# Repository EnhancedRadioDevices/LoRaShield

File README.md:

LoRaShield2.1 Hardware

These are the hardware design files for the LoRaShield2.1 electronics.

These hardware files were created with KiCAD. 
You may need the KiCAD libraries available here: https://github.com/mogar/KiCAD_libs
When opening these projects in KiCAD, you may need to change the path to the libraries from the above link.
This can be done in preferences->libraries in both the schematic editor and the layout editor.
Make sure the libraries noted there point to wherever you put the above KiCAD_libs repo.

# Arduino Library

Check out these libraries:

* https://github.com/EnhancedRadioDevices/LoRaHam
* https://github.com/EnhancedRadioDevices/LoRaChat

# LoRaShield 2.1 Pinout

LoRaShield uses the SPI pins on your Arduino. It also uses a couple of digital pins for reset and interrupt.

    Arduino <-> LoRaShield
    D2          interrupt
    D3          reset
    D10         SPI SS
    D11         SPI MOSI
    D12         SPI MISO
    D13         SPI SCK

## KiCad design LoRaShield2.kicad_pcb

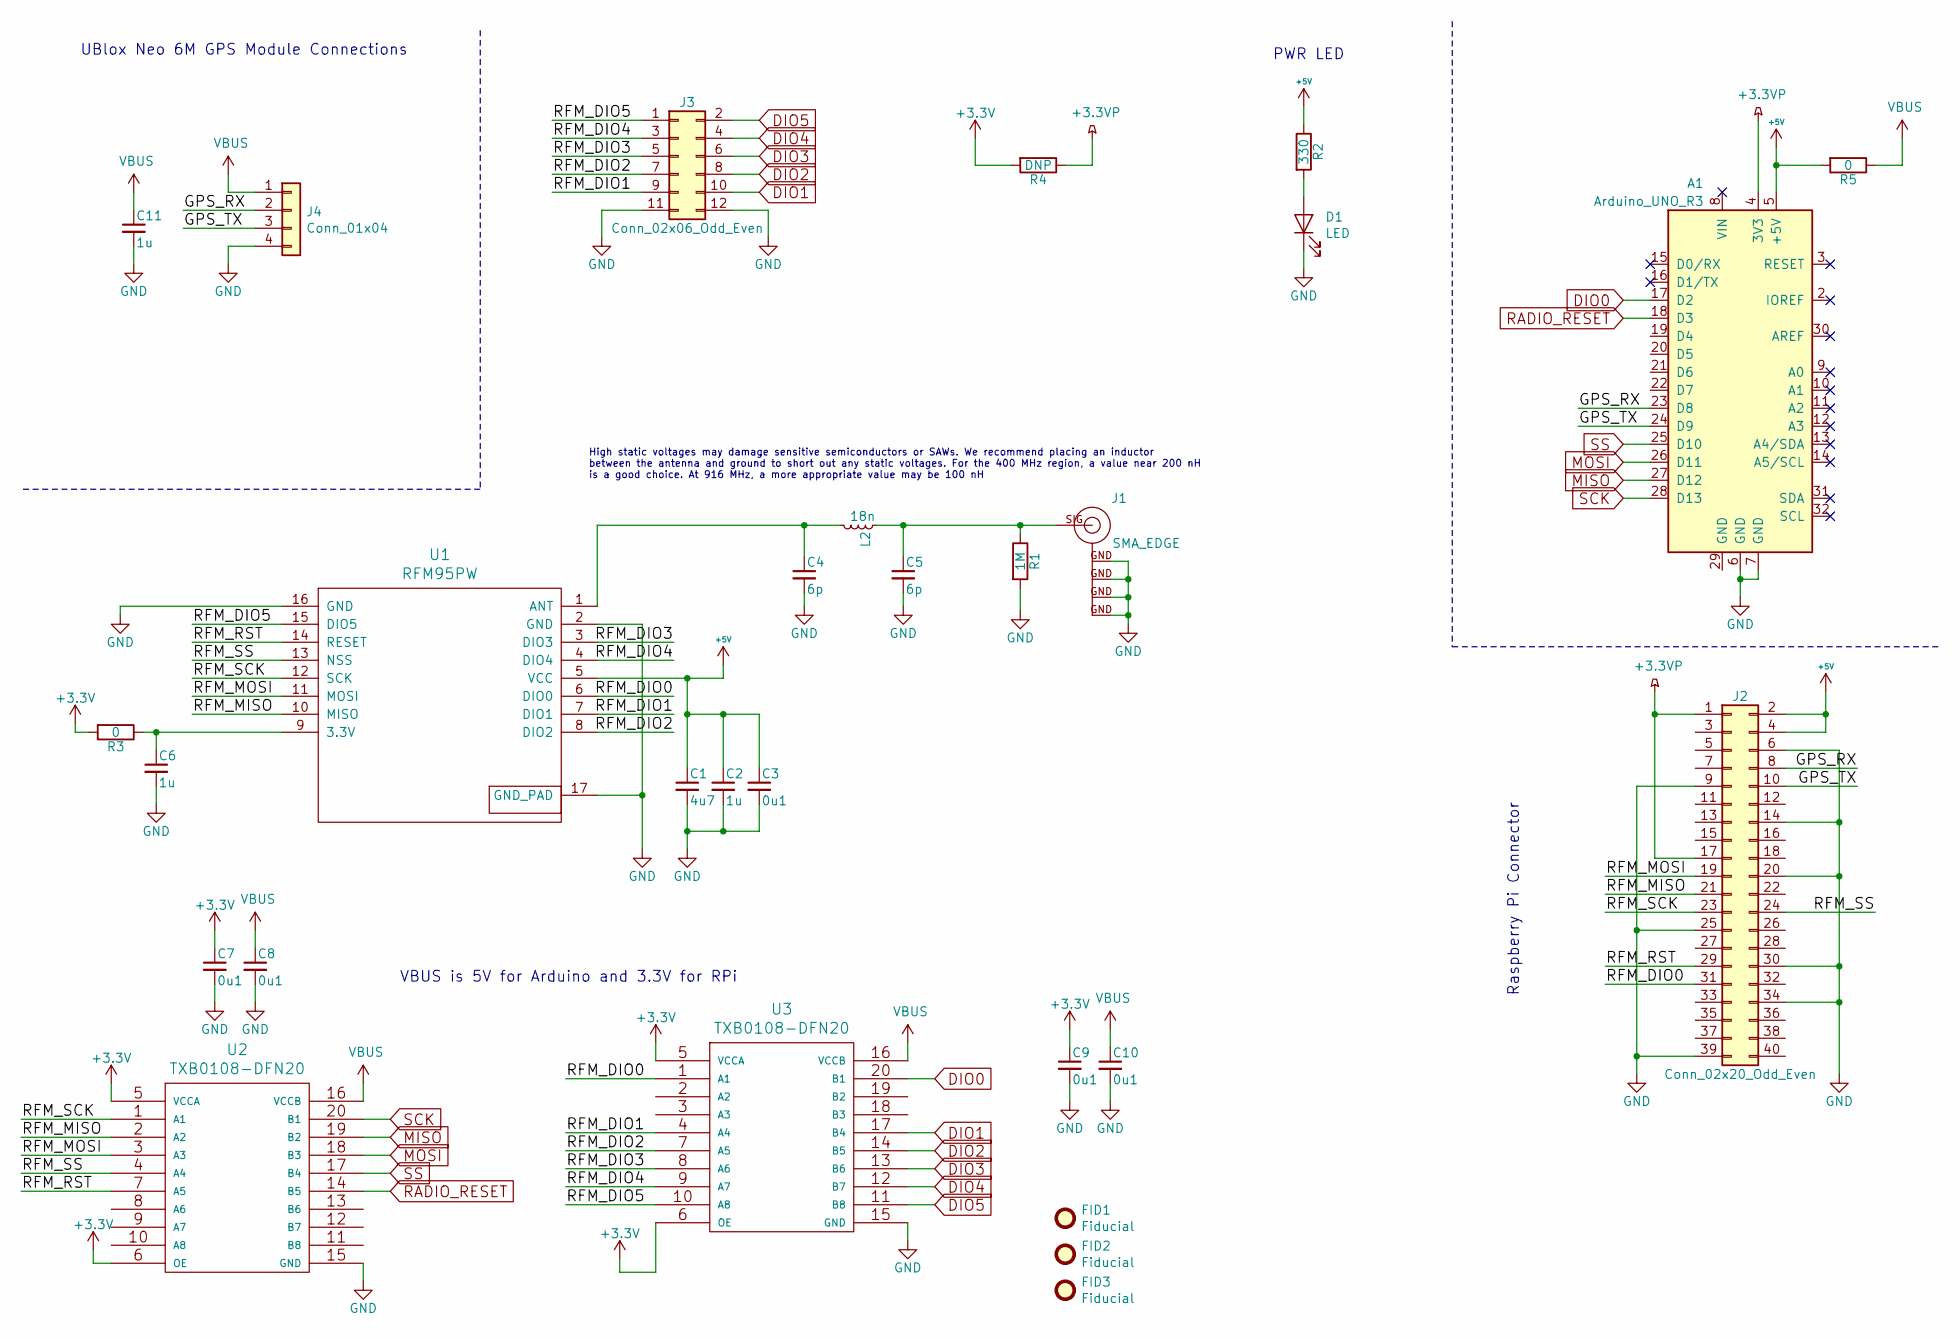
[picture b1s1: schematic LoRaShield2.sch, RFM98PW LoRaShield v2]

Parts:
A1: Arduino_UNO_R3; Arduino_UNO_HamShieldFootprint
C1: 4u7; C_0603
C2, C6, C11: 1u; C_0603
C3, C7, C8, C9, C10: 0u1; C_0603
C4, C5: 6p; C_0603
D1: LED; D_0603
FID1, FID2, FID3: Fiducial; Fiducial_0.5mm_Dia_1mm_Outer
J1: SMA_EDGE; SMA-EDGE-HandSolder
J2: Conn_02x20_Odd_Even; Pin_Header_Straight_2x20_Pitch2.54mm
J3: Conn_02x06_Odd_Even; Pin_Header_Straight_2x06_Pitch2.54mm
J4: Conn_01x04; Pin_Header_Straight_1x04_Pitch2.54mm
L2: 18n; L_0603
R1: 1M; R_0603
R2: 330; R_0603
R3, R5: 0; R_0402
R4: DNP; R_0402
U1: RFM95PW; RFM98PW
U2, U3: TXB0108-DFN20; USON-20_2x4mm_Pitch0.4mm

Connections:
+3.3VP: A1.4 (3V3), J2.1, J2.17, R4.1
+3V3: C7.1, C9.1, R3.2, R4.2, U2.5 (VCCA), U2.6 (OE), U3.5 (VCCA), U3.6 (OE)
+5V: A1.5 (+5V), C1.1, C2.1, C3.1, J2.2, J2.4, R2.1, R5.2, U1.5 (VCC)
/GPS_RX: A1.23 (D8), J2.8, J4.2
/GPS_TX: A1.24 (D9), J2.10, J4.3
/RFM_DIO0: J2.31, U1.6 (DIO0), U3.1 (A1)
/RFM_DIO1: J3.9, U1.7 (DIO1), U3.4 (A4)
/RFM_DIO2: J3.7, U1.8 (DIO2), U3.7 (A5)
/RFM_DIO3: J3.5, U1.3 (DIO3), U3.8 (A6)
/RFM_DIO4: J3.3, U1.4 (DIO4), U3.9 (A7)
/RFM_DIO5: J3.1, U1.15 (DIO5), U3.10 (A8)
/RFM_MISO: J2.21, U1.10 (MISO), U2.2 (A2)
/RFM_MOSI: J2.19, U1.11 (MOSI), U2.3 (A3)
/RFM_RST: J2.29, U1.14 (RESET), U2.7 (A5)
/RFM_SCK: J2.23, U1.12 (SCK), U2.1 (A1)
/RFM_SS: J2.24, U1.13 (NSS), U2.4 (A4)
DIO0: A1.17 (D2), U3.20 (B1)
DIO1: J3.10, U3.17 (B4)
DIO2: J3.8, U3.14 (B5)
DIO3: J3.6, U3.13 (B6)
DIO4: J3.4, U3.12 (B7)
DIO5: J3.2, U3.11 (B8)
GND: A1.6 (GND), A1.7 (GND), C1.2, C2.2, C3.2, C4.2, C5.2, C6.2, C7.2, C8.2, C9.2, C10.2, C11.2, D1.1 (K), J1.GND, J2.6, J2.9, J2.14, J2.20, J2.25, J2.30, J2.34, J2.39, J3.11, J3.12, J4.4, R1.2, U1.2 (GND), U1.16 (GND), U1.17 (GND_PAD), U2.15 (GND), U3.15 (GND)
MISO: A1.27 (D12), U2.19 (B2)
MOSI: A1.26 (D11), U2.18 (B3)
unnamed: C4.1, L2.2, U1.1 (ANT)
unnamed: C5.1, J1.SIG (SIGNAL), L2.1, R1.1
unnamed: C6.1, R3.1, U1.9 (3.3V)
unnamed: D1.2 (A), R2.2
RADIO_RESET: A1.18 (D3), U2.14 (B5)
SCK: A1.28 (D13), U2.20 (B1)
SS: A1.25 (D10), U2.17 (B4)
VBUS: C8.1, C10.1, C11.1, J4.1, R5.1, U2.16 (VCCB), U3.16 (VCCB)

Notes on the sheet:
High static voltages may damage sensitive semiconductors or SAWs. We recommend placing an inductor between the antenna and ground to short out any static voltages. For the 400 MHz region, a value near 200 nH is a good choice. At 916 MHz, a more appropriate value may be 100 nH
Raspberry Pi Connector
VBUS is 5V for Arduino and 3.3V for RPi
PWR LED
UBlox Neo 6M GPS Module Connections

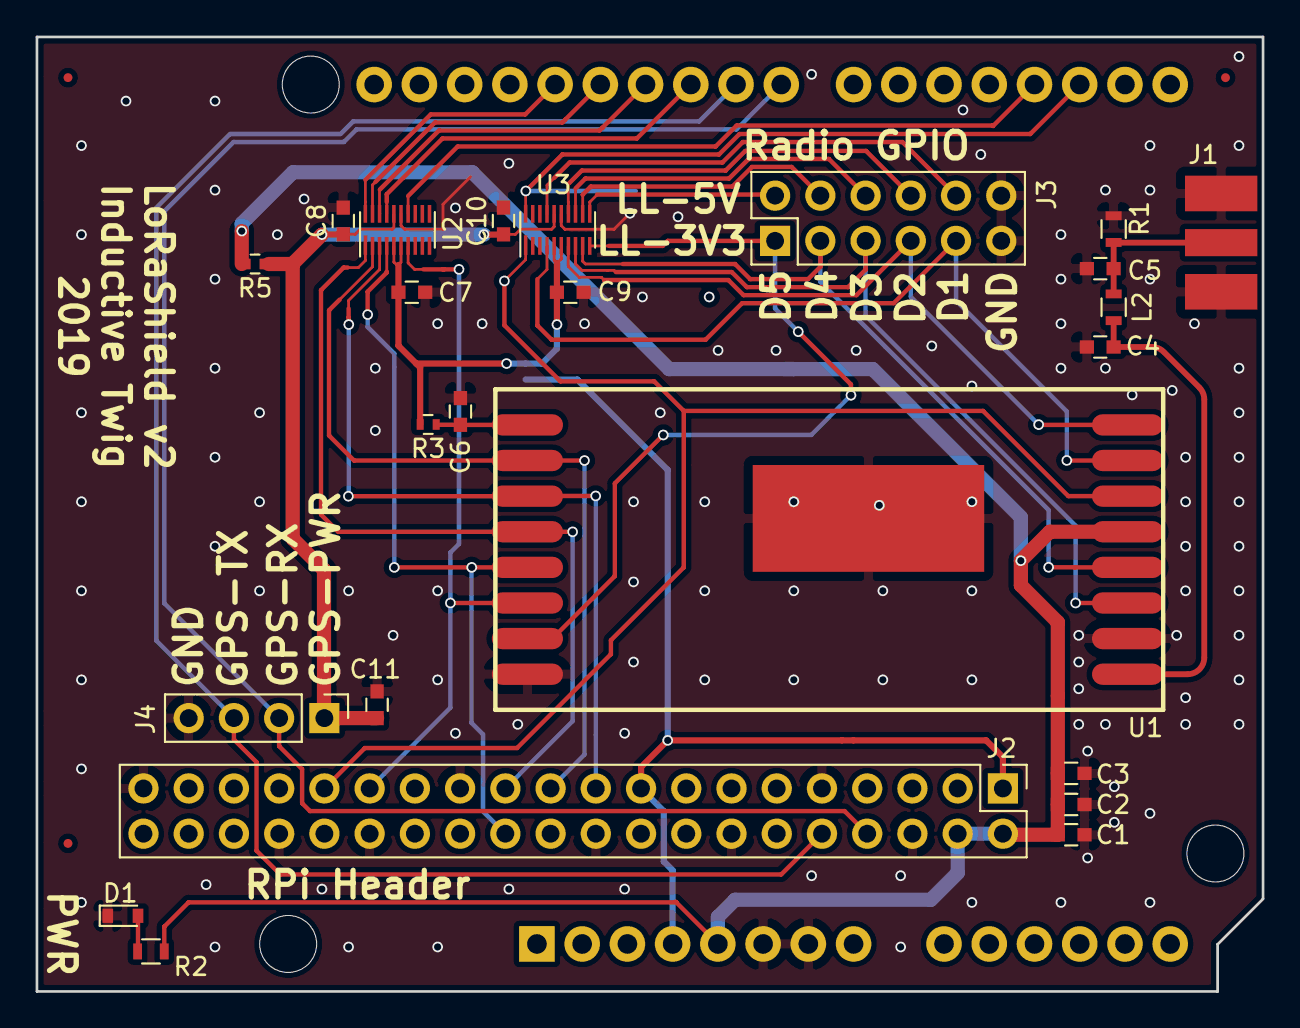
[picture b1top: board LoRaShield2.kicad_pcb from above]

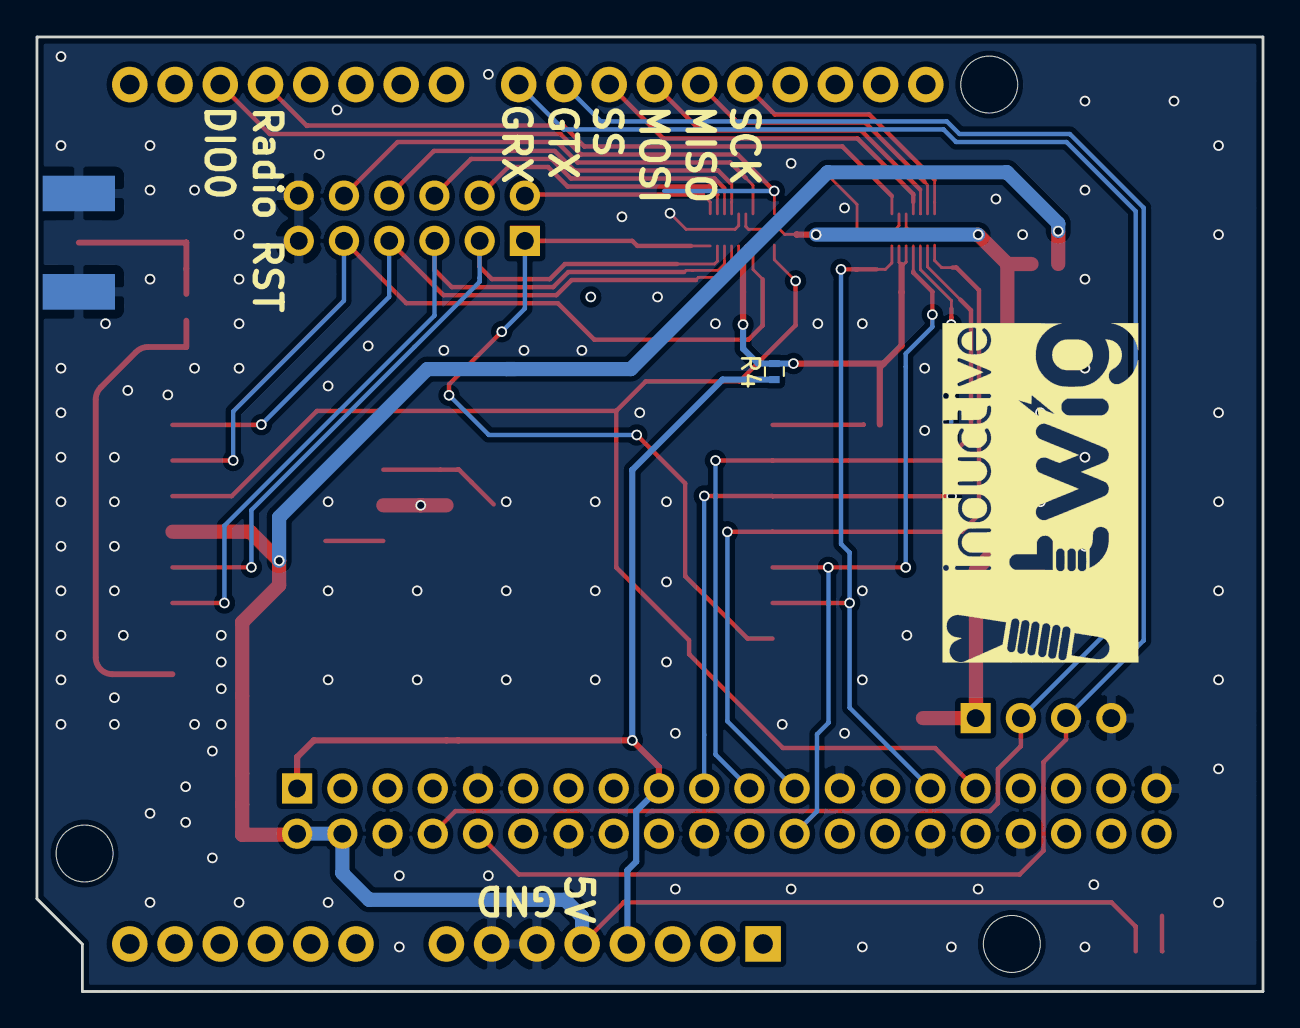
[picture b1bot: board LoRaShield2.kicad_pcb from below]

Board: 4 copper layers, 68.9 x 53.6 mm, 29 parts (2 on the bottom side), 33 nets.

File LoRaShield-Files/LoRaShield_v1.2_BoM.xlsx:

Id | Designator | Package | Quantity | Designation | MFR | MFR PN | Supplier | Supplier PN
1 | C1 | C_0603 | 1 | 4u7 | Samsung Electro-Mechanics | CL10A475MP5LNNC | DigiKey | 1276-6684-1-ND
2 | C2,C6 | C_0603 | 2 | 1u | Samsung Electro-Mechanics | CL10B105KP8NNNC | DigiKey | 1276-1946-1-ND
3 | C3,C7,C8,C9,C10 | C_0603 | 5 | 0u1 | Samsung Electro-Mechanics | CL10F104ZB8NNNC | DigiKey | 1276-1012-1-ND
4 | D1 | D_0603 | 1 | green LED | Lite-On | LTST-C190KGKT | DigiKey | 160-1435-2-ND
5 | J1 | SMA-EDGE-HandSolder | 1 | SMA_EDGE | DNP | DNP | DNP | DNP
6 | U1 | RFM98PW | 1 | RFM95PW | Hope RF | RFM95PW
7 | C4,C5 | C_0603 | 2 | 6p | Samsung Electro-Mechanics | CL10C060CB8NNNC | DigiKey | 1276-2133-1-ND
8 | L2 | L_0603 | 1 | 18n | Murata | LQW18AN18NJ00D | DigiKey | 490-1172-1-ND
9 | J2 | Pin_Header_Straight_2x20_Pitch2.54mm | 1 | Conn_02x20_Odd_Even | DNP | DNP | DNP | DNP
10 | U2,U3 | USON-20_2x4mm_Pitch0.4mm | 2 | TXB0108DQSR | Texas Instruments | TXB0108DQSR | DigiKey | 296-27217-1-ND
11 | R1 | R_0603 | 1 | 1M | Rohm Semiconductor | ESR03EZPJ105 | DigiKey | RHM1MDCT-ND
12 | R2 | R_0603 | 1 | 330 | Panasonic | ERJ-3GEYJ331V | DigiKey | P330GCT-ND
13 | J3 | Pin_Header_Straight_2x06_Pitch2.54mm | 1 | Conn_02x06_Odd_Even | DNP | DNP | DNP | DNP
14 | R3 | R_0402 | 1 | 0 | Vishay Dale | CRCW04020000Z0ED | DigiKey | 541-0.0JTR-ND
15 | R4 | R_0402 | 1 | DNP | DNP | DNP | DNP | DNP

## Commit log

2019-05-01 commiting hw files
2019-05-01 update files
2019-05-01 fab files added
2019-05-01 readme and ignore
